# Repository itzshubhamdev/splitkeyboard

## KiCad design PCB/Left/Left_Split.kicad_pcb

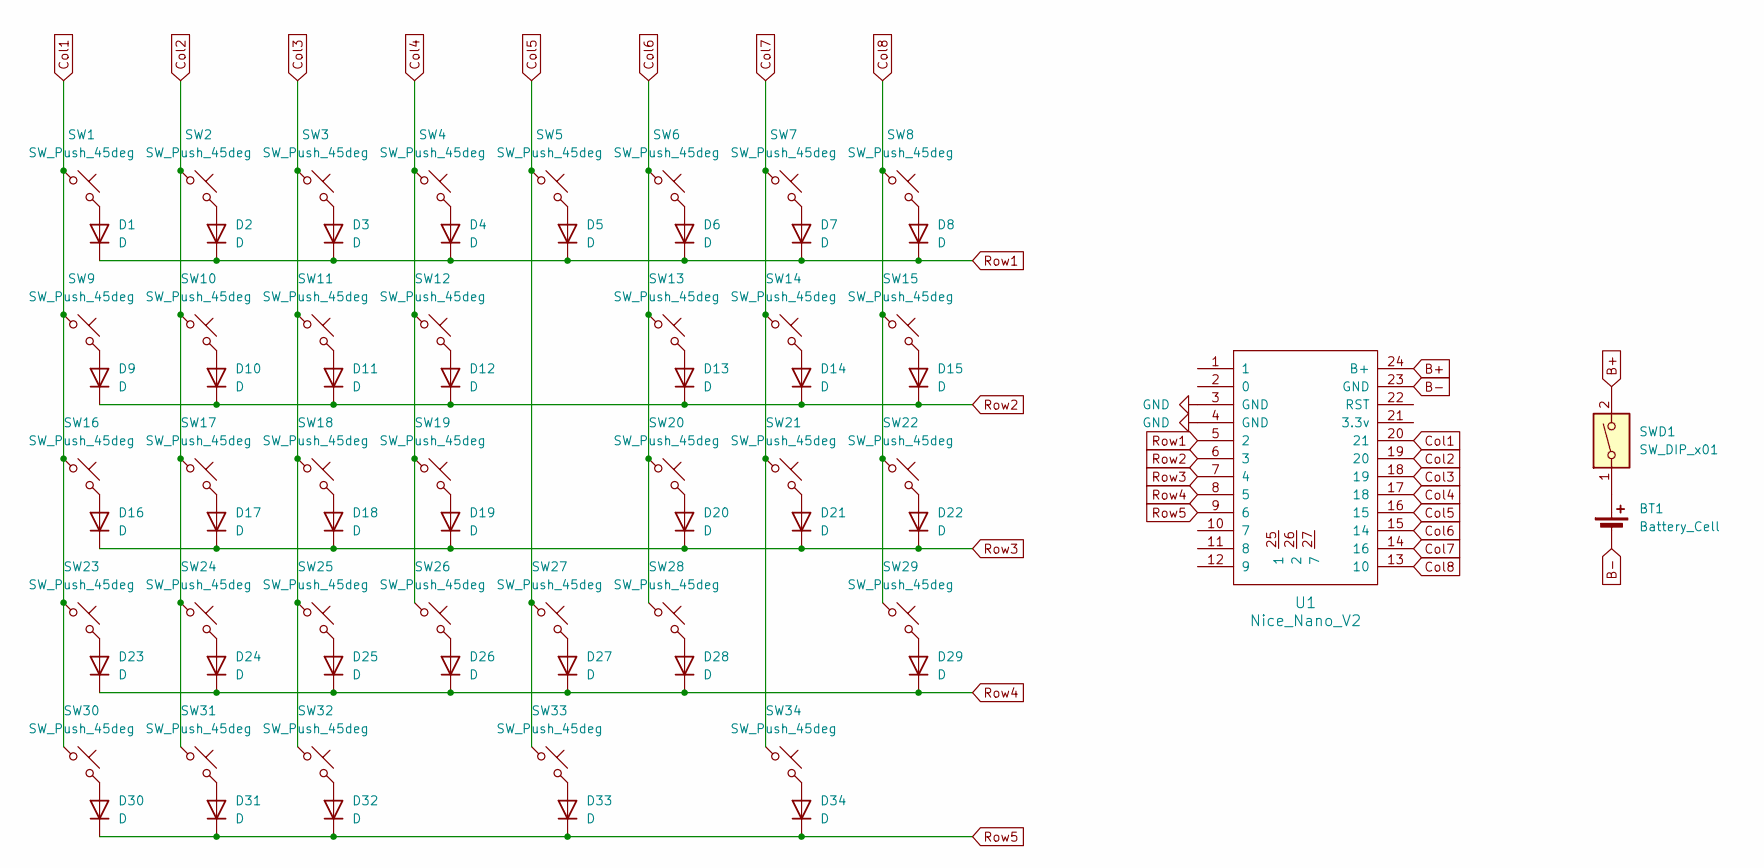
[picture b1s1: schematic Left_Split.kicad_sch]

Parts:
BT1: Battery_Cell; JST_PH_S2B-PH-K_1x02_P2.00mm_Horizontal
D1, D2, D3, D4, D5, D6, D7, D8, D9, D10, D11, D12, D13, D14, D15, D16, D17, D18, D19, D20, D21, D22, D23, D24, D25, D26, D27, D28, D29, D30, D31, D32, D33, D34: D; Diode_DO-35
SW1, SW2, SW3, SW4, SW5, SW6, SW7, SW8, SW10, SW11, SW12, SW13, SW14, SW15, SW17, SW18, SW19, SW20, SW21, SW22, SW24, SW25, SW26, SW27, SW28, SW29: SW_Push_45deg; Hotswap_MX_1.00u
SW9: SW_Push_45deg; Hotswap_MX_1.50u
SW16: SW_Push_45deg; Hotswap_MX_1.75u
SW23: SW_Push_45deg; Hotswap_MX_2.25u
SW30, SW31, SW32, SW33: SW_Push_45deg; Hotswap_MX_1.25u
SW34: SW_Push_45deg; Hotswap_MX_2.75u
SWD1: SW_DIP_x01; Switch_K3-1204D
U1: Nice_Nano_V2

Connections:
B+: SWD1.2, U1.24 (B+)
B-: BT1.2 (-), U1.23 (GND)
Col1: SW1.1, SW9.1, SW16.1, SW23.1, SW30.1, U1.20 (21)
Col2: SW2.1, SW10.1, SW17.1, SW24.1, SW31.1, U1.19 (20)
Col3: SW3.1, SW11.1, SW18.1, SW25.1, SW32.1, U1.18 (19)
Col4: SW4.1, SW12.1, SW19.1, SW26.1, U1.17 (18)
Col5: SW5.1, SW27.1, SW33.1, U1.16 (15)
Col6: SW6.1, SW13.1, SW20.1, SW28.1, U1.15 (14)
Col7: SW7.1, SW14.1, SW21.1, SW34.1, U1.14 (16)
Col8: SW8.1, SW15.1, SW22.1, SW29.1, U1.13 (10)
GND: U1.3 (GND), U1.4 (GND)
unnamed: BT1.1 (+), SWD1.1
unnamed: D1.2 (A), SW1.2
unnamed: D2.2 (A), SW2.2
unnamed: D3.2 (A), SW3.2
unnamed: D4.2 (A), SW4.2
unnamed: D5.2 (A), SW5.2
unnamed: D6.2 (A), SW6.2
unnamed: D7.2 (A), SW7.2
unnamed: D8.2 (A), SW8.2
unnamed: D9.2 (A), SW9.2
unnamed: D10.2 (A), SW10.2
unnamed: D11.2 (A), SW11.2
unnamed: D12.2 (A), SW12.2
unnamed: D13.2 (A), SW13.2
unnamed: D14.2 (A), SW14.2
unnamed: D15.2 (A), SW15.2
unnamed: D16.2 (A), SW16.2
unnamed: D17.2 (A), SW17.2
unnamed: D18.2 (A), SW18.2
unnamed: D19.2 (A), SW19.2
unnamed: D20.2 (A), SW20.2
unnamed: D21.2 (A), SW21.2
unnamed: D22.2 (A), SW22.2
unnamed: D23.2 (A), SW23.2
unnamed: D24.2 (A), SW24.2
unnamed: D25.2 (A), SW25.2
unnamed: D26.2 (A), SW26.2
unnamed: D27.2 (A), SW27.2
unnamed: D28.2 (A), SW28.2
unnamed: D29.2 (A), SW29.2
unnamed: D30.2 (A), SW30.2
unnamed: D31.2 (A), SW31.2
unnamed: D32.2 (A), SW32.2
unnamed: D33.2 (A), SW33.2
unnamed: D34.2 (A), SW34.2
Row1: D1.1 (K), D2.1 (K), D3.1 (K), D4.1 (K), D5.1 (K), D6.1 (K), D7.1 (K), D8.1 (K), U1.5 (2)
Row2: D9.1 (K), D10.1 (K), D11.1 (K), D12.1 (K), D13.1 (K), D14.1 (K), D15.1 (K), U1.6 (3)
Row3: D16.1 (K), D17.1 (K), D18.1 (K), D19.1 (K), D20.1 (K), D21.1 (K), D22.1 (K), U1.7 (4)
Row4: D23.1 (K), D24.1 (K), D25.1 (K), D26.1 (K), D27.1 (K), D28.1 (K), D29.1 (K), U1.8 (5)
Row5: D30.1 (K), D31.1 (K), D32.1 (K), D33.1 (K), D34.1 (K), U1.9 (6)

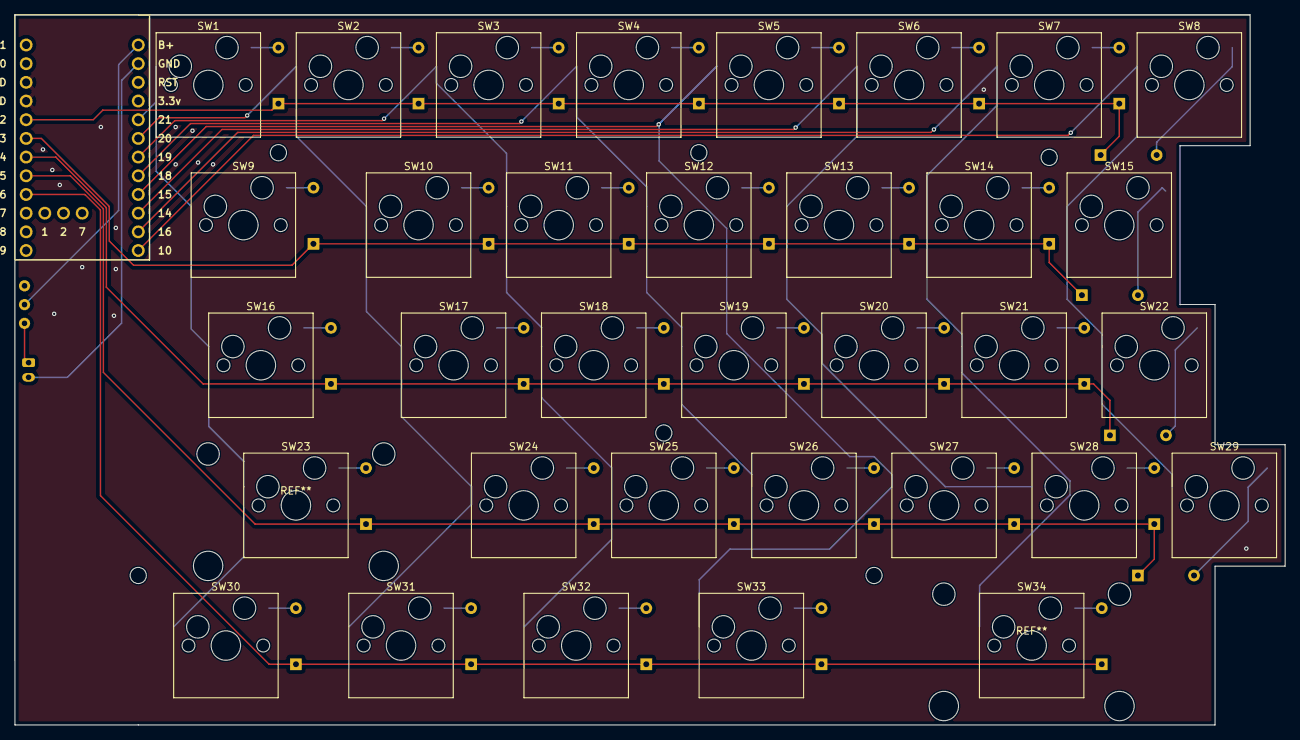
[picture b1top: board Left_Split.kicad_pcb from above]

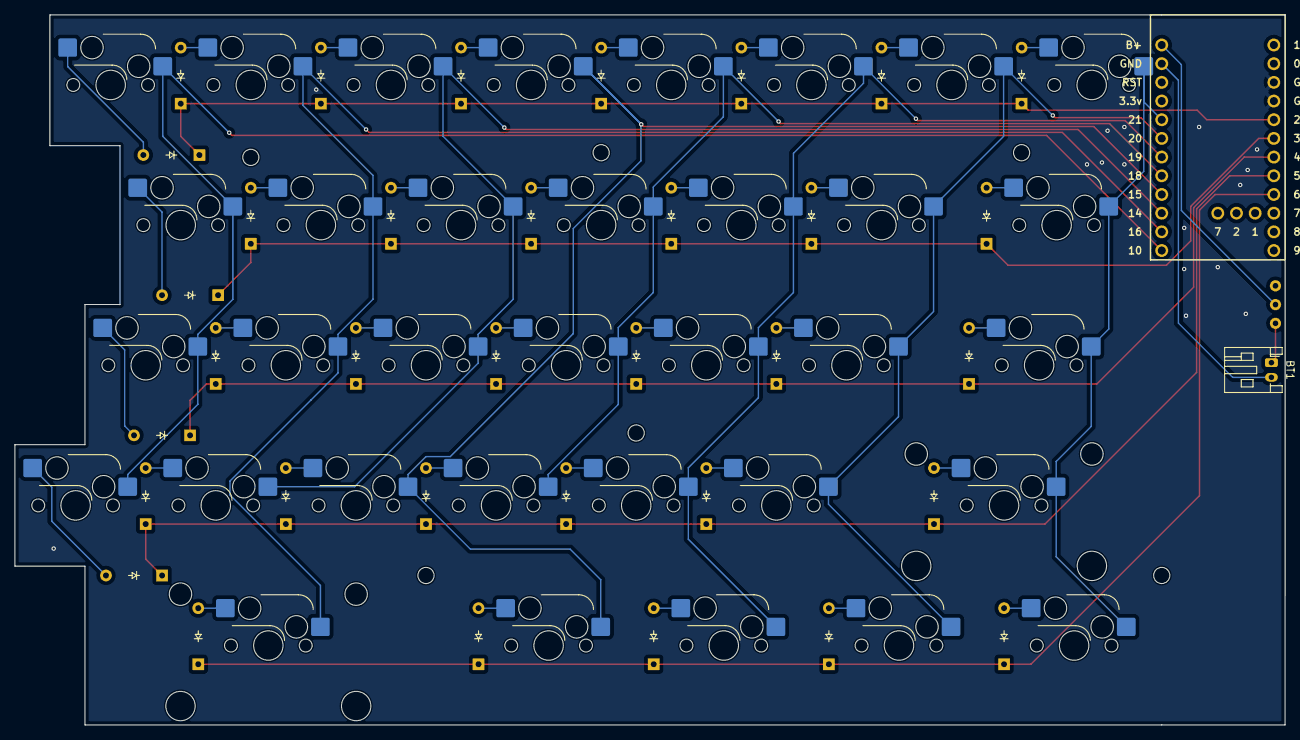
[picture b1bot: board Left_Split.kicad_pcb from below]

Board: 2 copper layers, 172.7 x 96.5 mm, 71 parts (35 on the bottom side), 51 nets.

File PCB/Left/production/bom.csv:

Designator,Footprint,Quantity,Value,LCSC Part #
BT1,JST_PH_S2B-PH-K_1x02_P2.00mm_Horizontal,1,Battery_Cell,
"D1, D10, D11, D12, D13, D14, D15, D16, D17, D18, D19, D2, D20, D21, D22, D23, D24, D25, D26, D27, D28, D29, D3, D30, D31, D32, D33, D34, D4, D5, D6, D7, D8, D9",Diode_DO-35,34,D,
"SW1, SW10, SW11, SW12, SW13, SW14, SW15, SW17, SW18, SW19, SW2, SW20, SW21, SW22, SW24, SW25, SW26, SW27, SW28, SW29, SW3, SW4, SW5, SW6, SW7, SW8",Hotswap_MX_1.00u,26,SW_Push_45deg,
SW16,Hotswap_MX_1.75u,1,SW_Push_45deg,
SW23,Hotswap_MX_2.25u,1,SW_Push_45deg,
"SW30, SW31, SW32, SW33",Hotswap_MX_1.25u,4,SW_Push_45deg,
SW34,Hotswap_MX_2.75u,1,SW_Push_45deg,
SW9,Hotswap_MX_1.50u,1,SW_Push_45deg,
SWD1,Switch_K3-1204D,1,SW_DIP_x01,C145861
U1,Nice_Nano_V2,1,Nice_Nano_V2,

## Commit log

2026-03-31 Add PCB and CAD files and images
